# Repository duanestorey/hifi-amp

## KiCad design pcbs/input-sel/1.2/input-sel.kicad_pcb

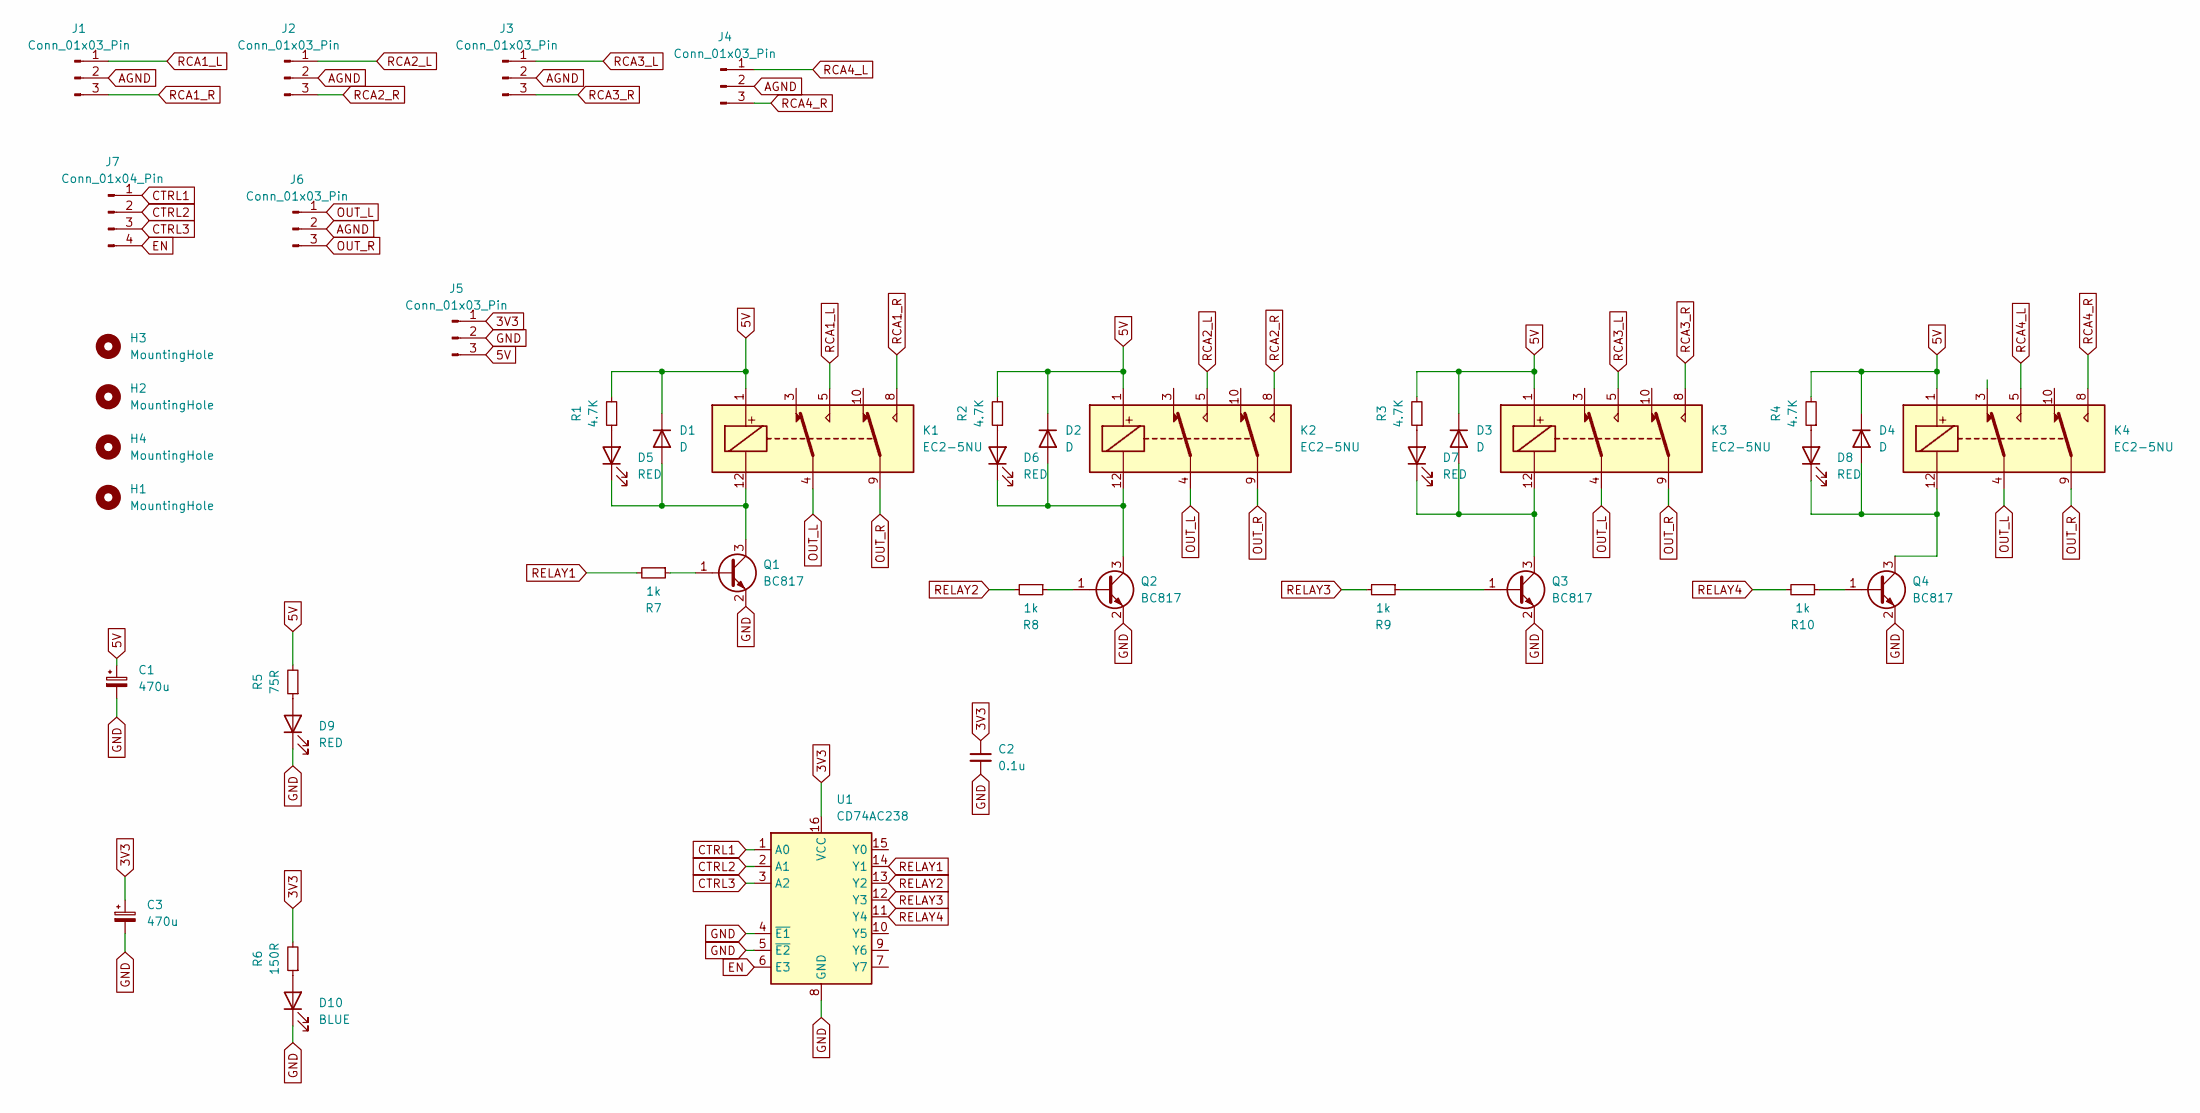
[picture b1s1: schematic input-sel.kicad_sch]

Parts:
C1, C3: 470u; CP_Radial_D6.3mm_P2.50mm
C2: 0.1u; C_0603_1608Metric
D1, D2, D3, D4: D; D_SMA; Mouser 863-NRVA4005T3G
D5, D6, D7, D8, D9: RED; LED_0603_1608Metric
D10: BLUE; LED_0603_1608Metric
H1, H2, H3, H4: MountingHole; MountingHole_3.2mm_M3_DIN965_Pad_TopOnly
J1, J2, J3, J4, J5, J6: Conn_01x03_Pin; JST_PH_B3B-PH-K_1x03_P2.00mm_Vertical
J7: Conn_01x04_Pin; JST_PH_B4B-PH-K_1x04_P2.00mm_Vertical
K1, K2, K3, K4: EC2-5NU; KEMET EA2; Mouser 80-EA2-12NU
Q1, Q2, Q3, Q4: BC817; SOT-23
R1, R2, R3, R4: 4.7K; R_0603_1608Metric_Pad0.98x0.95mm_HandSolder
R5: 75R; R_0603_1608Metric_Pad0.98x0.95mm_HandSolder
R6: 150R; R_0603_1608Metric_Pad0.98x0.95mm_HandSolder
R7, R8, R9, R10: 1k; R_0603_1608Metric_Pad0.98x0.95mm_HandSolder; Mouser 603-AC0603JR-07820RL
U1: CD74AC238; TSSOP-16_4.4x5mm_P0.65mm; Mouser 512-74AC138MTCX

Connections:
3V3: C2.1, C3.1, J5.1, R6.2, U1.16 (VCC)
5V: C1.1, D1.1 (K), D2.1 (K), D3.1 (K), D4.1 (K), J5.3, K1.1, K2.1, K3.1, K4.1, R1.2, R2.2, R3.2, R4.2, R5.2
AGND: J1.2, J2.2, J3.2, J4.2, J6.2
CTRL1: J7.1, U1.1 (A0)
CTRL2: J7.2, U1.2 (A1)
CTRL3: J7.3, U1.3 (A2)
EN: J7.4, U1.6 (E3)
GND: C1.2, C2.2, C3.2, D9.1 (K), D10.1 (K), J5.2, Q1.2 (E), Q2.2 (E), Q3.2 (E), Q4.2 (E), U1.4 (~E1), U1.5 (~E2), U1.8 (GND)
unnamed: D1.2 (A), D5.1 (K), K1.12, Q1.3 (C)
unnamed: D2.2 (A), D6.1 (K), K2.12, Q2.3 (C)
unnamed: D3.2 (A), D7.1 (K), K3.12, Q3.3 (C)
unnamed: D4.2 (A), D8.1 (K), K4.12, Q4.3 (C)
unnamed: D5.2 (A), R1.1
unnamed: D6.2 (A), R2.1
unnamed: D7.2 (A), R3.1
unnamed: D8.2 (A), R4.1
unnamed: D9.2 (A), R5.1
unnamed: D10.2 (A), R6.1
unnamed: Q1.1 (B), R7.1
unnamed: Q2.1 (B), R8.1
unnamed: Q3.1 (B), R9.1
unnamed: Q4.1 (B), R10.1
OUT_L: J6.1, K1.4, K2.4, K3.4, K4.4
OUT_R: J6.3, K1.9, K2.9, K3.9, K4.9
RCA1_L: J1.1, K1.5
RCA1_R: J1.3, K1.8
RCA2_L: J2.1, K2.5
RCA2_R: J2.3, K2.8
RCA3_L: J3.1, K3.5
RCA3_R: J3.3, K3.8
RCA4_L: J4.1, K4.5
RCA4_R: J4.3, K4.8
RELAY1: R7.2, U1.14 (Y1)
RELAY2: R8.2, U1.13 (Y2)
RELAY3: R9.2, U1.12 (Y3)
RELAY4: R10.2, U1.11 (Y4)

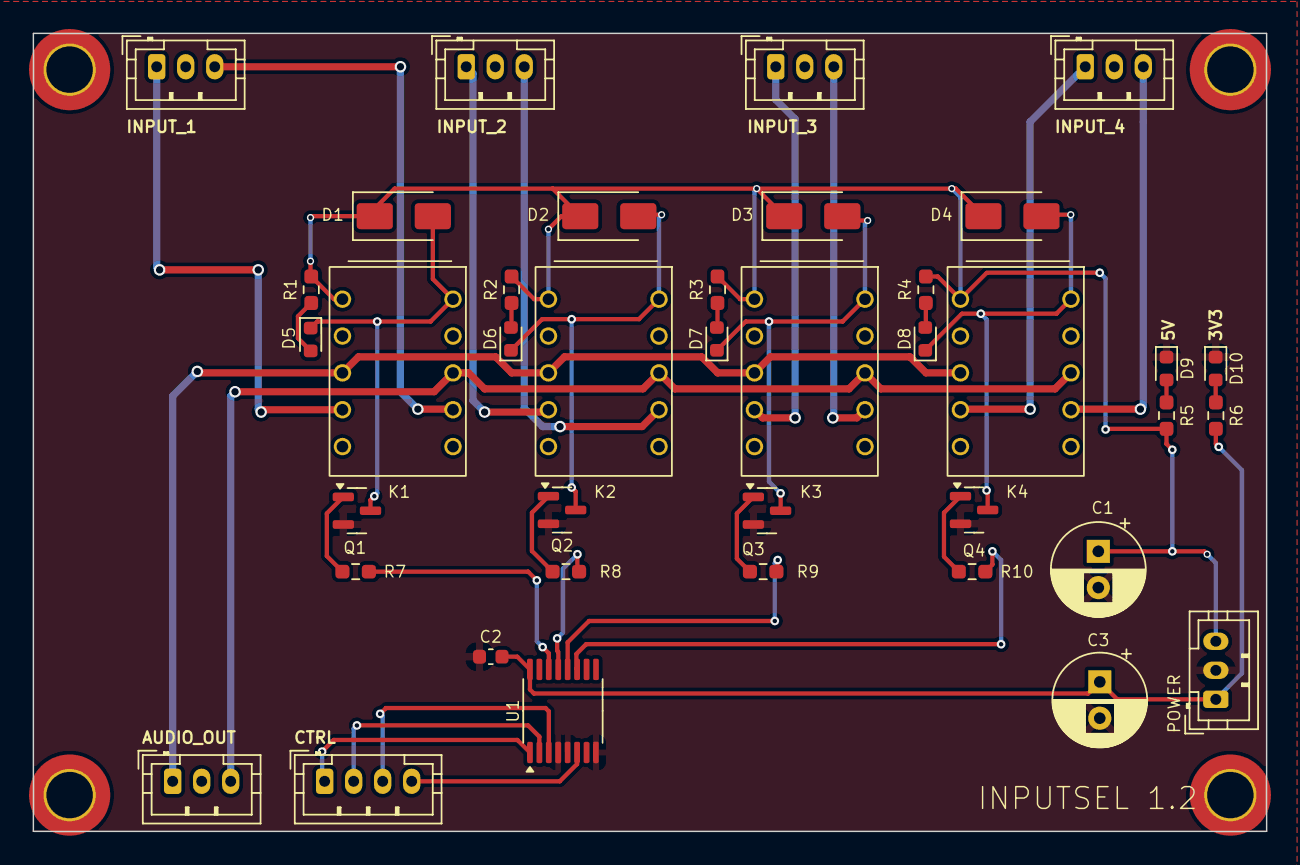
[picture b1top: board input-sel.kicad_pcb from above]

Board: 2 copper layers, 85.0 x 55.0 mm, 43 parts (0 on the bottom side), 36 nets.

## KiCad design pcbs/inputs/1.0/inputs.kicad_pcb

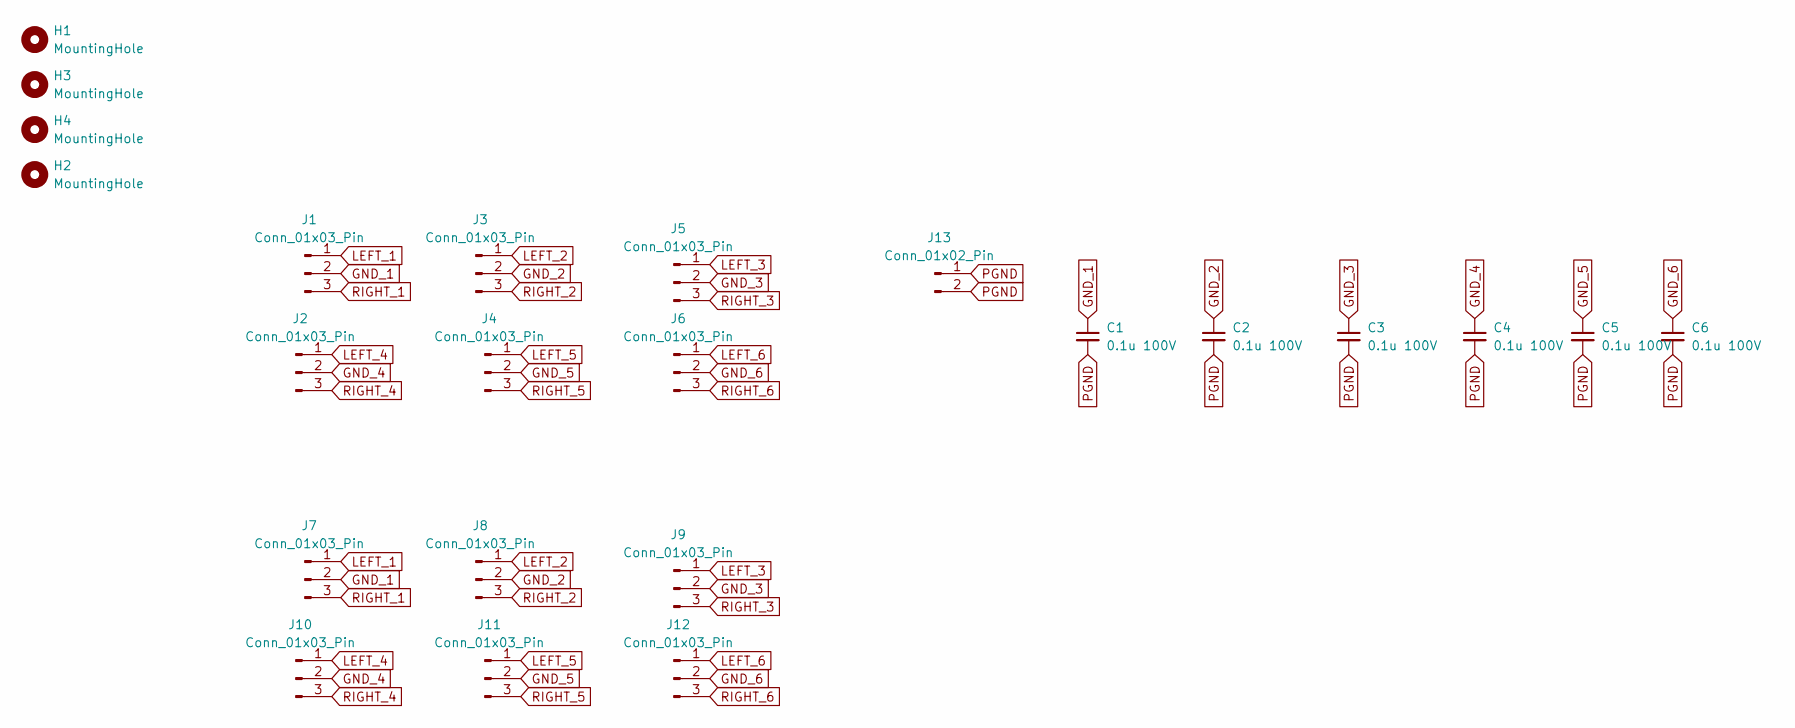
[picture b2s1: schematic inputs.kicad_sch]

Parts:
C1, C2, C3, C4, C5, C6: 0.1u 100V; C_1206_3216Metric; Mouser 791-1206B104K101CT
H1, H2, H3, H4: MountingHole; MountingHole_3.2mm_M3_DIN965_Pad_TopOnly
J1, J2, J3, J4, J5, J6, J7, J8, J9, J10, J11, J12: Conn_01x03_Pin; JST_PH_B3B-PH-K_1x03_P2.00mm_Vertical
J13: Conn_01x02_Pin; JST_VH_B2P-VH-B_1x02_P3.96mm_Vertical

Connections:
GND_1: C1.1, J1.2, J7.2
GND_2: C2.1, J3.2, J8.2
GND_3: C3.1, J5.2, J9.2
GND_4: C4.1, J2.2, J10.2
GND_5: C5.1, J4.2, J11.2
GND_6: C6.1, J6.2, J12.2
LEFT_1: J1.1, J7.1
LEFT_2: J3.1, J8.1
LEFT_3: J5.1, J9.1
LEFT_4: J2.1, J10.1
LEFT_5: J4.1, J11.1
LEFT_6: J6.1, J12.1
PGND: C1.2, C2.2, C3.2, C4.2, C5.2, C6.2, J13.1, J13.2
RIGHT_1: J1.3, J7.3
RIGHT_2: J3.3, J8.3
RIGHT_3: J5.3, J9.3
RIGHT_4: J2.3, J10.3
RIGHT_5: J4.3, J11.3
RIGHT_6: J6.3, J12.3

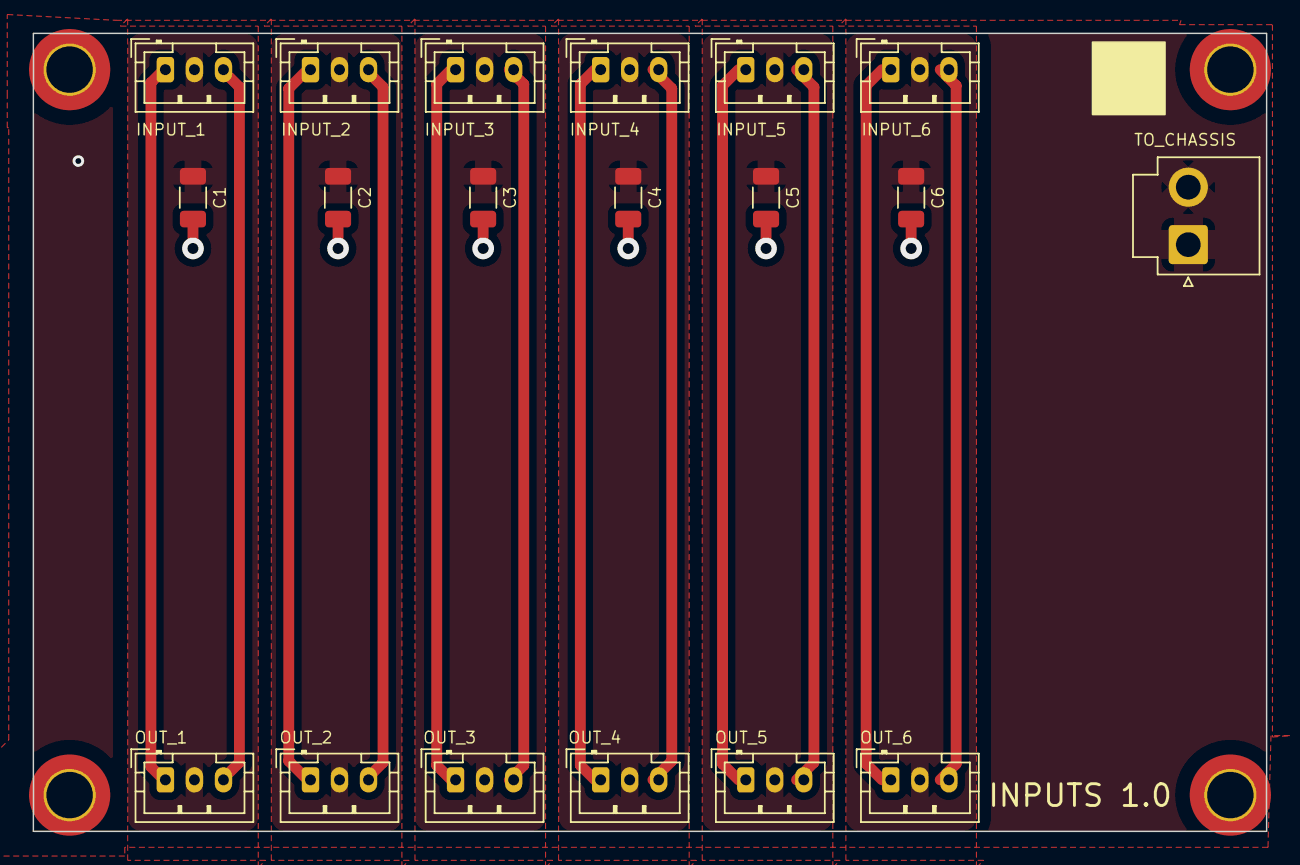
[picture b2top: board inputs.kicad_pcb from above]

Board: 2 copper layers, 85.0 x 55.0 mm, 23 parts (0 on the bottom side), 19 nets.

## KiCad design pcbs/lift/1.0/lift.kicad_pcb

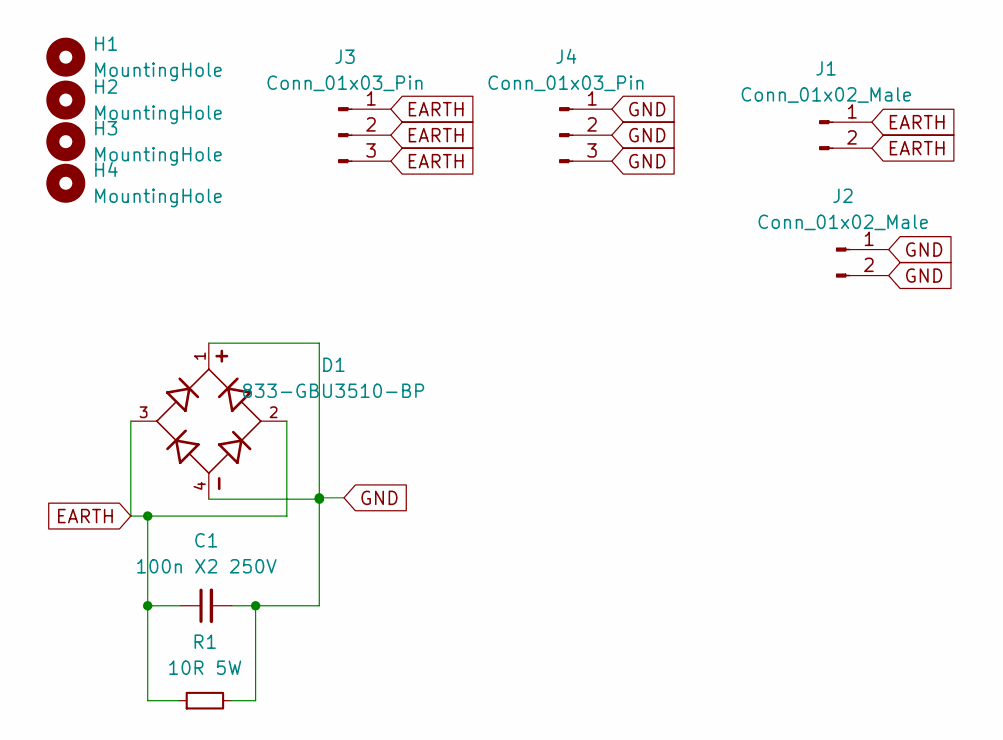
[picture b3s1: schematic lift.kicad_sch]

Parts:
C1: 100n X2 250V; C_Rect_L18.0mm_W5.0mm_P15.00mm_FKS3_FKP3; Mouser 871-B32922X2104K000
D1: 833-GBU3510-BP; Diode_Bridge_Vishay_GBU; Mouser 833-GBU3510-BP
H1, H2, H3, H4: MountingHole; MountingHole_3.2mm_M3_DIN965_Pad_TopOnly
J1, J2: Conn_01x02_Male; JST_VH_B2P-VH-B_1x02_P3.96mm_Vertical
J3, J4: Conn_01x03_Pin; TerminalBlock_Phoenix_PT-1,5-3-5.0-H_1x03_P5.00mm_Horizontal
R1: 10R 5W; R_Axial_DIN0617_L17.0mm_D6.0mm_P25.40mm_Horizontal; Mouser 594-AC05W10R00J

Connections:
EARTH: C1.1, D1.2, D1.3, J1.1, J1.2, J3.1, J3.2, J3.3, J3.4, R1.1
GND: C1.2, D1.1, D1.4, J2.1, J2.2, J4.1, J4.2, J4.3, J4.4, R1.2

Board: 2 copper layers, 11 parts (0 on the bottom side), 2 nets, no tracks yet.

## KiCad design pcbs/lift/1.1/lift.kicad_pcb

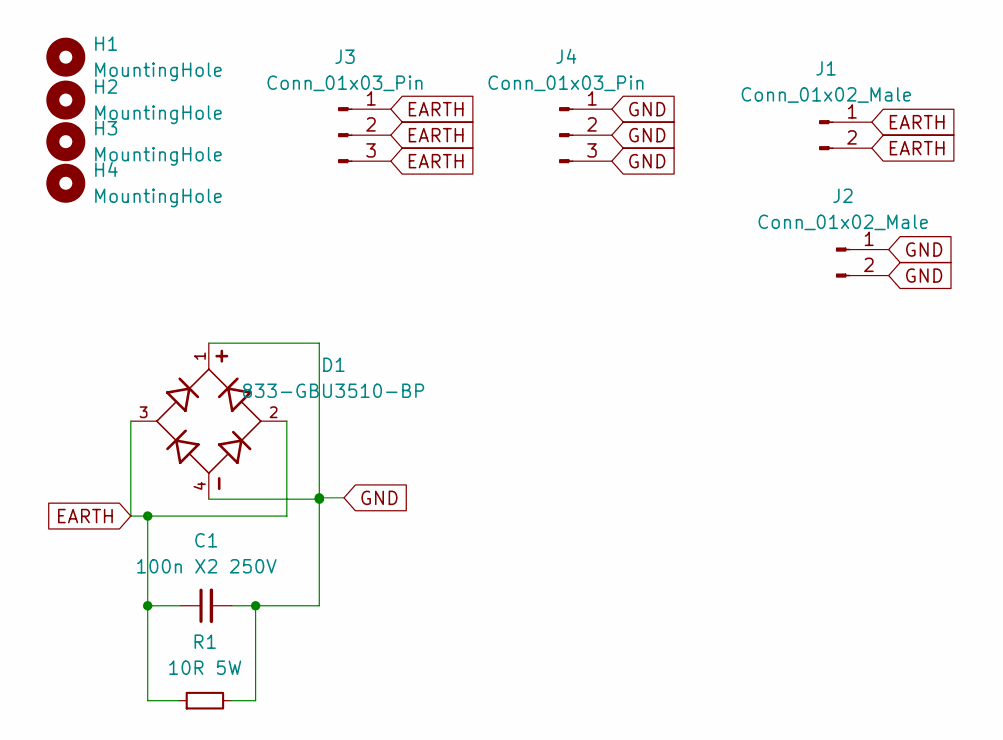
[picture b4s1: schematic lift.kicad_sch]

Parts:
C1: 100n X2 250V; C_Rect_L18.0mm_W5.0mm_P15.00mm_FKS3_FKP3; Mouser 871-B32922X2104K000
D1: 833-GBU3510-BP; Diode_Bridge_Vishay_GBU; Mouser 833-GBU3510-BP
H1, H2, H3, H4: MountingHole; MountingHole_3.2mm_M3_DIN965_Pad_TopOnly
J1, J2: Conn_01x02_Male; JST_VH_B2P-VH-B_1x02_P3.96mm_Vertical
J3, J4: Conn_01x03_Pin; TerminalBlock_Phoenix_PT-1,5-3-5.0-H_1x03_P5.00mm_Horizontal
R1: 10R 5W; R_Axial_DIN0617_L17.0mm_D6.0mm_P25.40mm_Horizontal; Mouser 594-AC05W10R00J

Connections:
EARTH: C1.1, D1.2, D1.3, J1.1, J1.2, J3.1, J3.2, J3.3, R1.1
GND: C1.2, D1.1, D1.4, J2.1, J2.2, J4.1, J4.2, J4.3, R1.2

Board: 2 copper layers, 11 parts (0 on the bottom side), 2 nets, no tracks yet.

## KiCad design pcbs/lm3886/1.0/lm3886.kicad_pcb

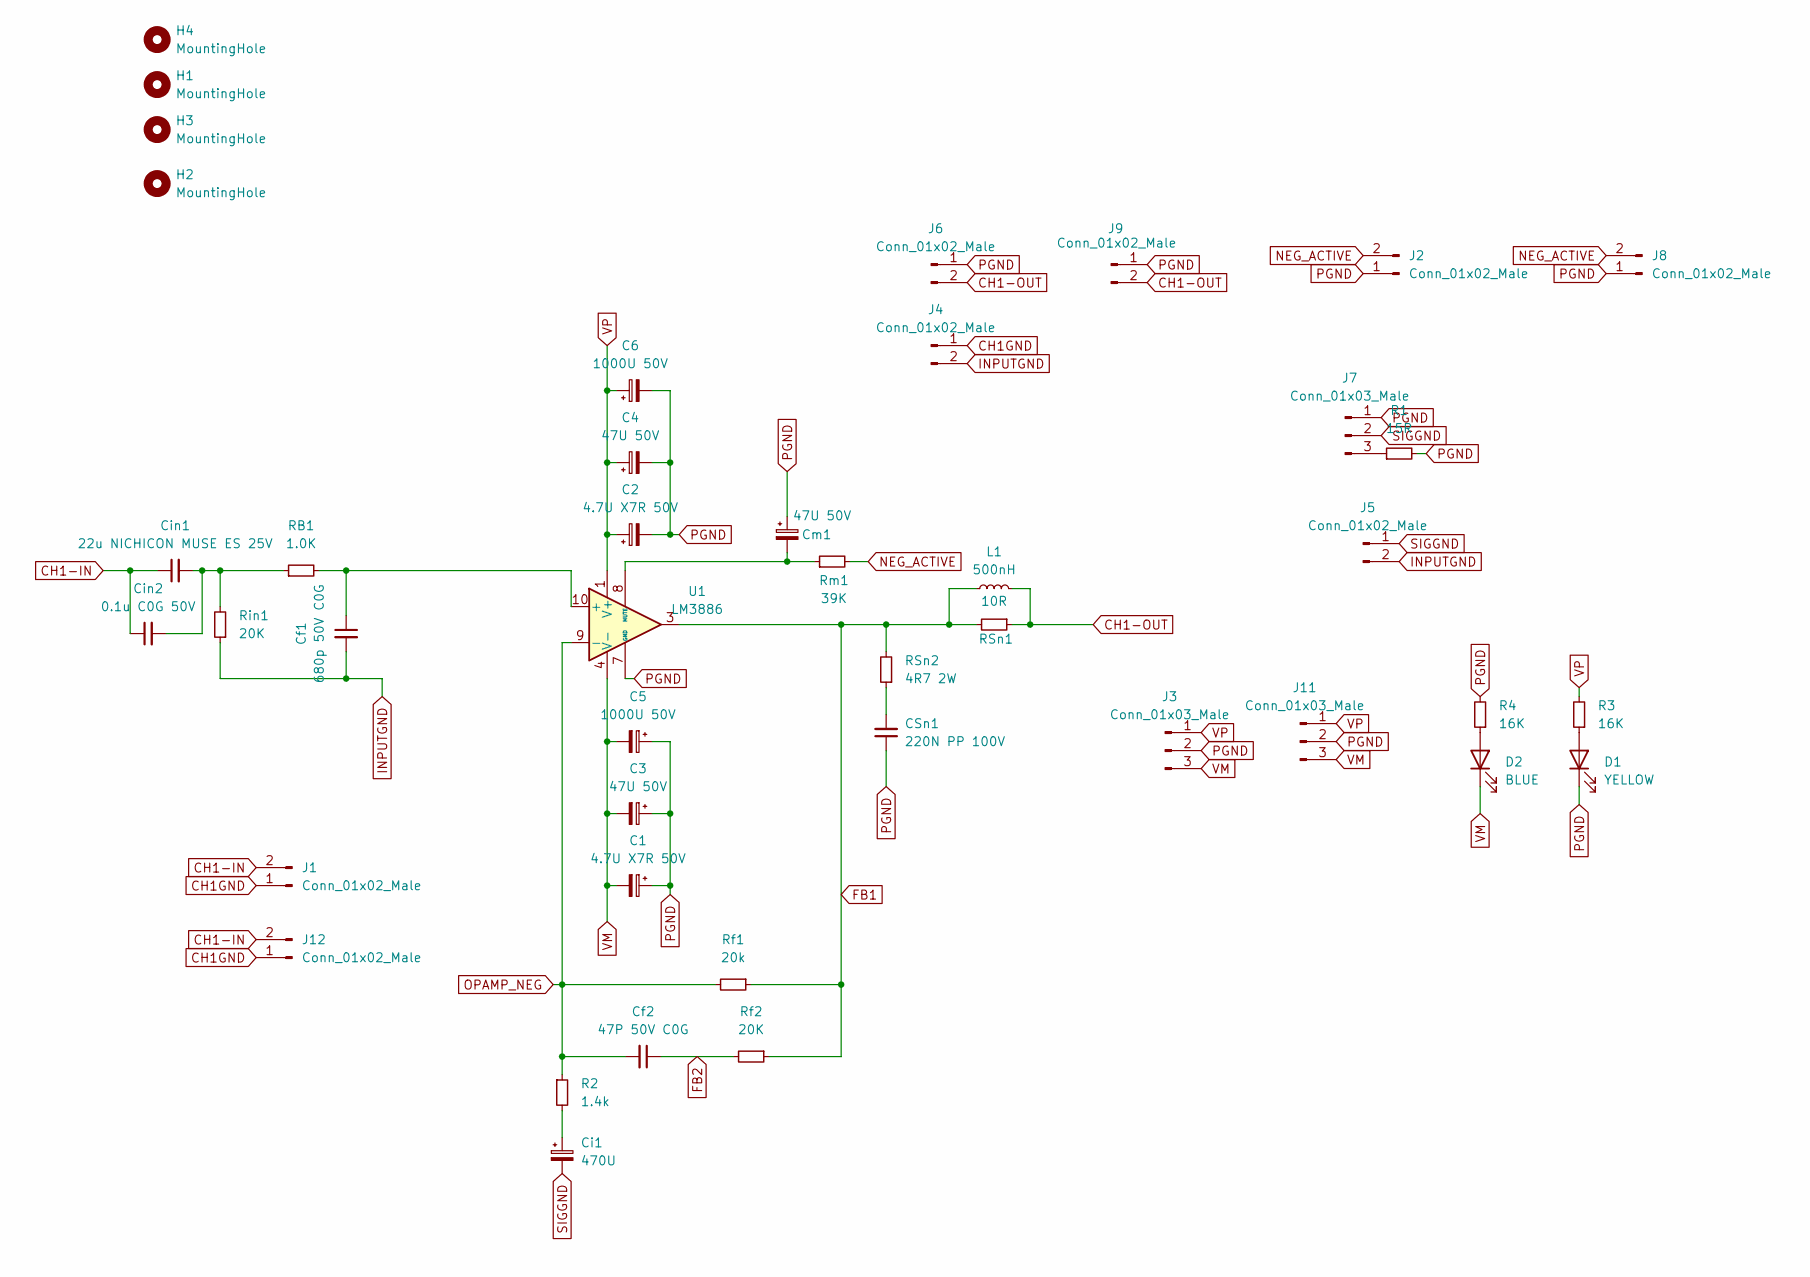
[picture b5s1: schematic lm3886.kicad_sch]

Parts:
C1, C2: 4.7U X7R 50V; C_1206_3216Metric_Pad1.33x1.80mm_HandSolder; Mouser 80-C1206X475J5RACTU
C3, C4: 47U 50V; CP_Radial_D6.3mm_P2.50mm
C5, C6: 1000U 50V; CP_Radial_D12.5mm_P5.00mm
CSn1: 220N PP 100V; C_Rect_L18.0mm_W7.0mm_P15.00mm_FKS3_FKP3; Mouser 505-MKP1D032204D00JB
Cf1: 680p 50V C0G; C_1206_3216Metric_Pad1.33x1.80mm_HandSolder; Mouser 603-CC126GRNPO9BN681
Cf2: 47P 50V C0G; C_1206_3216Metric_Pad1.33x1.80mm_HandSolder; Mouser 791-1206N470F500CT
Ci1: 470U; CP_Radial_D12.5mm_P5.00mm
Cin1: 22u NICHICON MUSE ES 25V; C_Radial_D6.3mm_H5.0mm_P2.50mm
Cin2: 0.1u C0G 50V; C_1206_3216Metric_Pad1.33x1.80mm_HandSolder; Mouser 81-GRT31C5C1H104FA2L
Cm1: 47U 50V; CP_Radial_D6.3mm_P2.50mm
D1: YELLOW; LED_0603_1608Metric_Pad1.05x0.95mm_HandSolder
D2: BLUE; LED_0603_1608Metric_Pad1.05x0.95mm_HandSolder
H1, H2, H3, H4: MountingHole; M3 Slot
J1, J2, J8, J12: Conn_01x02_Male; JST_PH_B2B-PH-K_1x02_P2.00mm_Vertical
J3, J11: Conn_01x03_Male; JST_VH_B3P-VH-B_1x03_P3.96mm_Vertical
J4, J5: Conn_01x02_Male; PinHeader_1x02_P2.54mm_Vertical
J6, J9: Conn_01x02_Male; JST_VH_B2P-VH_1x02_P3.96mm_Vertical
J7: Conn_01x03_Male; PinHeader_1x03_P2.54mm_Vertical
L1: 500nH; 500nH Inductor Aliexpress Air Gap
R1: 15R; R_1206_3216Metric_Pad1.30x1.75mm_HandSolder
R2: 1.4k; R_1206_3216Metric_Pad1.30x1.75mm_HandSolder; Mouser 603-RT1206FRE07750RL
R3, R4: 16K; R_0603_1608Metric_Pad0.98x0.95mm_HandSolder
RB1: 1.0K; R_1206_3216Metric_Pad1.30x1.75mm_HandSolder; Mouser 603-RT1206FRE131KL
RSn1: 10R; R_4020_10251Metric_Pad1.65x5.30mm_HandSolder; Mouser 279-355010RJT
RSn2: 4R7 2W; R_2512_6332Metric_Pad1.40x3.35mm_HandSolder; Mouser 603-RC2512JK-7W4R7
Rf1: 20k; R_1206_3216Metric_Pad1.30x1.75mm_HandSolder; Mouser 603-RT1206FRD0720KL
Rf2: 20K; R_1206_3216Metric_Pad1.30x1.75mm_HandSolder; Mouser 603-RT1206FRD0720KL
Rin1: 20K; R_1206_3216Metric_Pad1.30x1.75mm_HandSolder; Mouser 603-RT1206FRD0720KL
Rm1: 39K; R_1206_3216Metric_Pad1.30x1.75mm_HandSolder; Mouser 603-RC1206JR-0739KL
U1: LM3886; TO-220-11_P3.4x5.08mm_StaggerOdd_Lead4.85mm_Vertical

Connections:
CH1-IN: Cin1.1, Cin2.1, J1.2, J12.2
CH1-OUT: J6.2, J9.2, L1.2, RSn1.1
CH1GND: J1.1, J4.1, J12.1
FB1: L1.1, RSn1.2, RSn2.2, Rf1.1, Rf2.1, U1.3
FB2: Cf2.1, Rf2.2
INPUTGND: Cf1.2, J4.2, J5.2, Rin1.1
NEG_ACTIVE: J2.2, J8.2, Rm1.2
unnamed: CSn1.2, RSn2.1
unnamed: Ci1.1, R2.2
unnamed: Cin1.2, Cin2.2, RB1.1, Rin1.2
unnamed: D1.2 (A), R3.1
unnamed: D2.2 (A), R4.1
unnamed: J7.3, R1.1
unnamed: Cf1.1, RB1.2, U1.10 (+)
unnamed: Cm1.2, Rm1.1, U1.8 (MUTE)
OPAMP_NEG: Cf2.2, R2.1, Rf1.2, U1.9 (-)
PGND: C1.1, C2.2, C3.1, C4.2, C5.1, C6.2, CSn1.1, Cm1.1, D1.1 (K), J2.1, J3.2, J6.1, J7.1, J8.1, J9.1, J11.2, R1.2, R4.2, U1.7 (GND)
SIGGND: Ci1.2, J5.1, J7.2
VM: C1.2, C3.2, C5.2, D2.1 (K), J3.3, J11.3, U1.4 (V-)
VP: C2.1, C4.1, C6.1, J3.1, J11.1, R3.2, U1.1 (V+), U1.5 (V+)

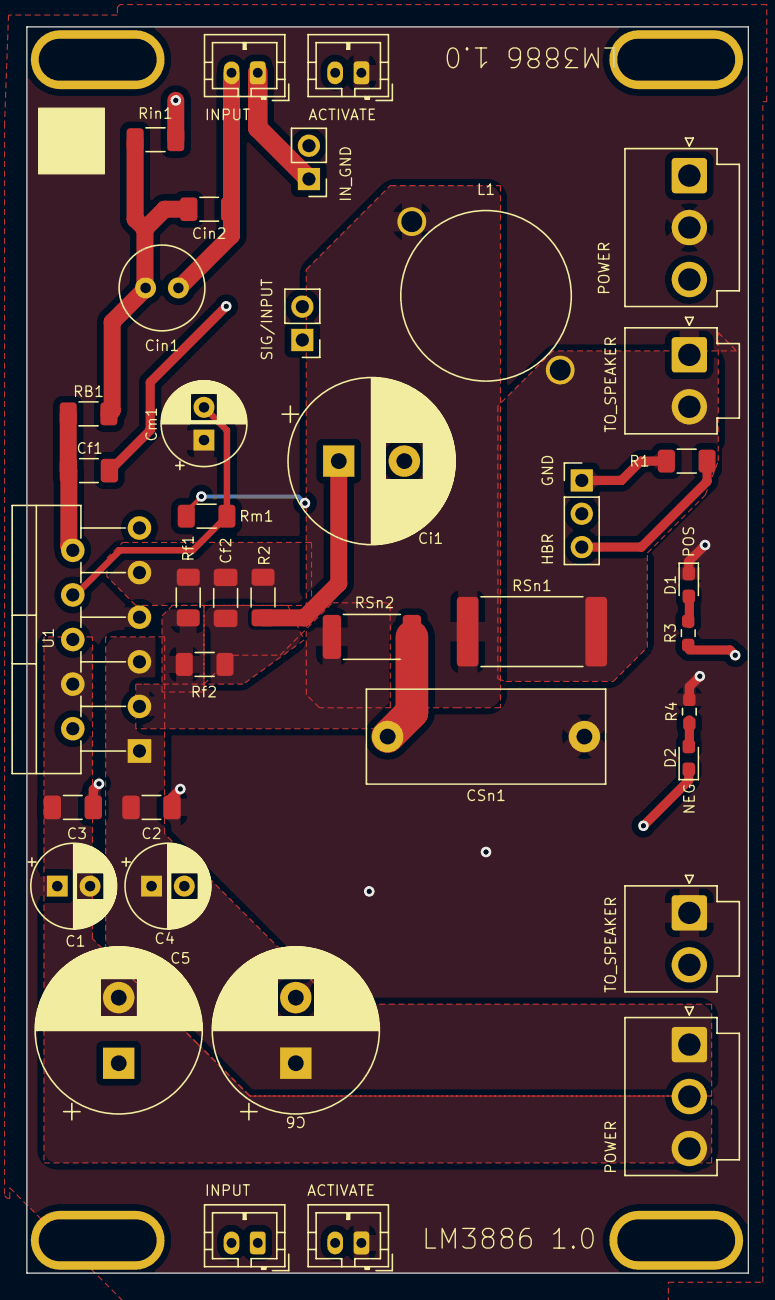
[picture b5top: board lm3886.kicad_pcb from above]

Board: 4 copper layers, 55.0 x 95.0 mm, 43 parts (0 on the bottom side), 20 nets.
